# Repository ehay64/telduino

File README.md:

# Telduino

## Summary
Telduino is an Arduino shield for land line telephones. Telduino has the ability to send and receive audio to and from land line telephones, as well as make them ring.

## Background
Over the last few years, I've been collecting interesting land line telephones here and there. Since land line service is nearly defunct as of this writing, I figured it would be neat to have a device that could pipe audio to and from a telephone and, more importantly, make them ring. This culminated in an Arduino shield that can be connected to a telephone.

## Details
The heart of this shield is the KS0835F SLIC (subscriber line interface circuit) module. This module provides all the required voltages, currents, and signals to the telephone. It also provides line level audio input and output. The module itself requires some signaling, which is provided by the Arduino.

The shield has two 3.5mm audio jacks for audio input and output, and a RJ11 jack for the telephone. The Arduino sketch controls ringing of the telephone by controlling the SLIC module.

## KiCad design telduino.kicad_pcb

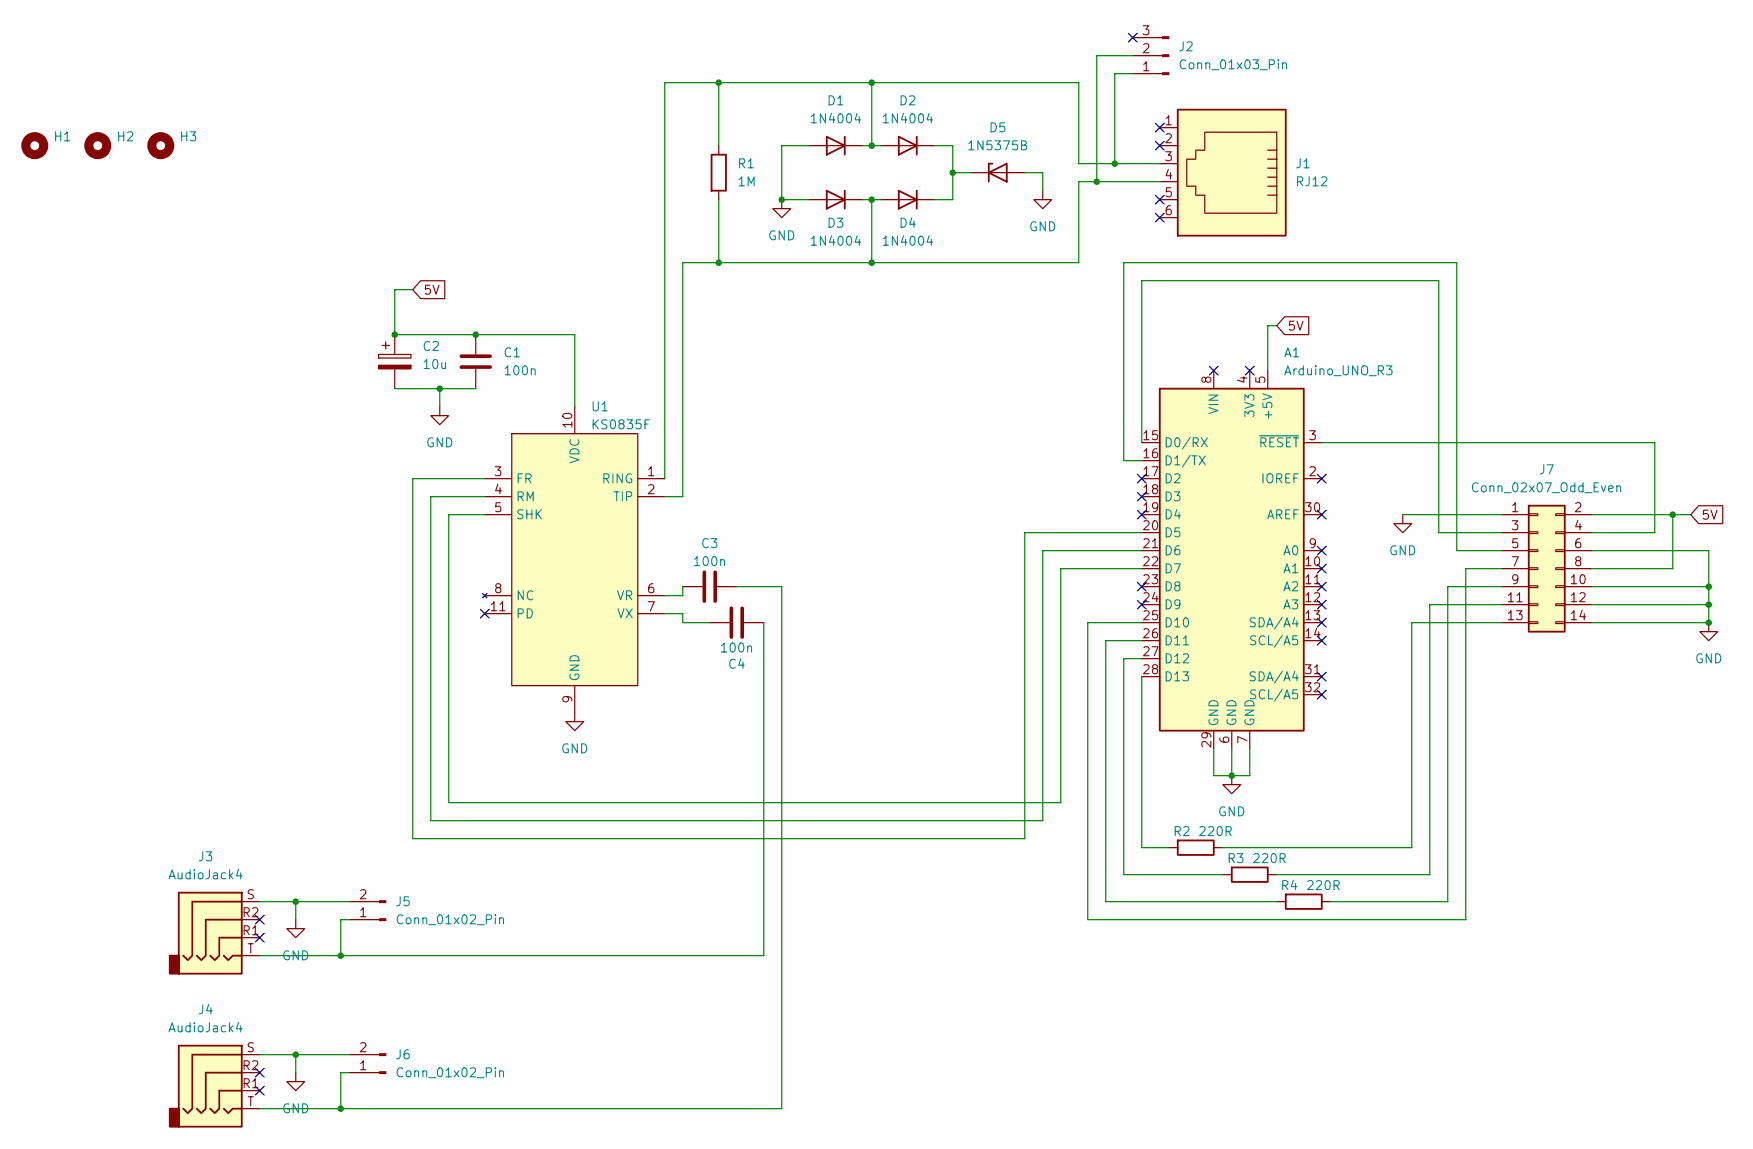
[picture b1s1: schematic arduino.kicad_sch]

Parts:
A1: Arduino_UNO_R3
C1, C3, C4: 100n; C_0805_2012Metric_Pad1.18x1.45mm_HandSolder
C2: 10u; CP_EIA-3216-18_Kemet-A_Pad1.58x1.35mm_HandSolder
D1, D2, D3, D4: 1N4004; D_DO-41_SOD81_P10.16mm_Horizontal
D5: 1N5375B; D_DO-201_P15.24mm_Horizontal
H1, H2, H3: MountingHole; MountingHole_3.2mm_M3
J1: RJ12; GCT_MJ3235-66-0_REVA
J2: Conn_01x03_Pin; PinHeader_1x03_P2.54mm_Vertical
J3, J4: AudioJack4; TENSILITY_54-00174
J5, J6: Conn_01x02_Pin; PinHeader_1x02_P2.54mm_Vertical
J7: Conn_02x07_Odd_Even; PinHeader_2x07_P2.54mm_Vertical
R1: 1M; R_Axial_DIN0207_L6.3mm_D2.5mm_P10.16mm_Horizontal
R2, R3, R4: 220R; R_0805_2012Metric_Pad1.20x1.40mm_HandSolder
U1: KS0835F

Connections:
5V: A1.5 (+5V), C1.1, C2.1, J7.2, J7.8, U1.10 (VDC)
GND: A1.6 (GND), A1.7 (GND), A1.29 (GND), C1.2, C2.2, D1.2 (A), D3.2 (A), D5.2 (A), J3.S, J4.S, J5.2, J6.2, J7.1, J7.6, J7.10, J7.12, J7.14, U1.9 (GND)
unnamed: A1.15 (D0/RX), J7.3
unnamed: A1.16 (D1/TX), J7.5
unnamed: A1.20 (D5), U1.3 (FR)
unnamed: A1.21 (D6), U1.4 (RM)
unnamed: A1.22 (D7), U1.5 (SHK)
unnamed: A1.25 (D10), J7.7
unnamed: A1.26 (D11), R4.2
unnamed: A1.27 (D12), R3.2
unnamed: A1.28 (D13), R2.2
unnamed: A1.3 (~RESET), J7.4
unnamed: D1.1 (K), D2.2 (A), J1.3, J2.1, R1.1, U1.1 (RING)
unnamed: D2.1 (K), D4.1 (K), D5.1 (K)
unnamed: D3.1 (K), D4.2 (A), J1.4, J2.2, R1.2, U1.2 (TIP)
unnamed: C4.2, J3.T, J5.1
unnamed: C3.2, J4.T, J6.1
unnamed: J7.9, R4.1
unnamed: J7.11, R3.1
unnamed: J7.13, R2.1
unnamed: C3.1, U1.6 (VR)
unnamed: C4.1, U1.7 (VX)

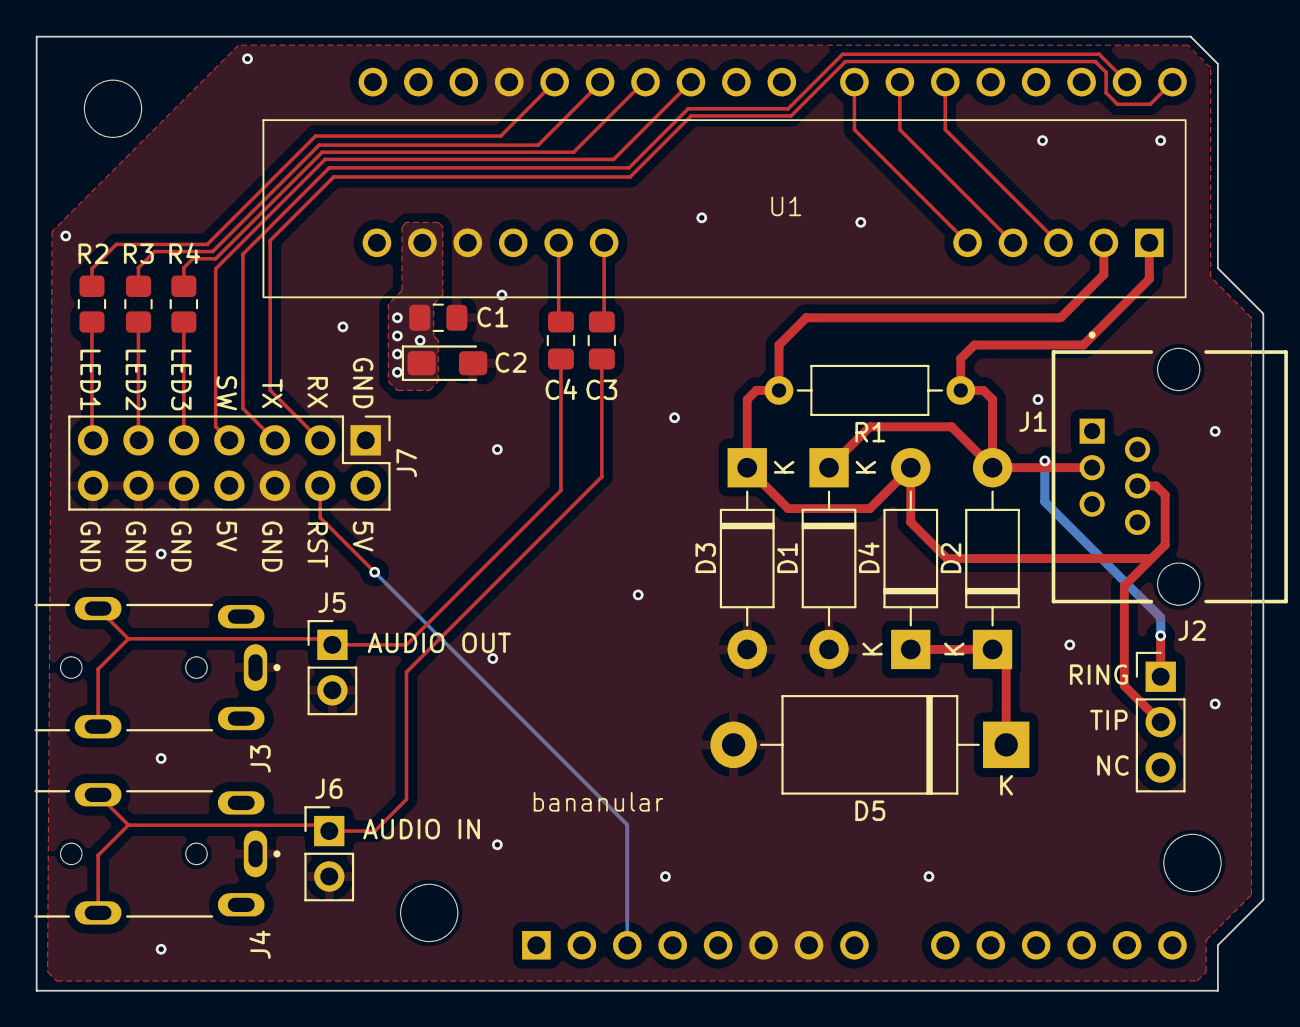
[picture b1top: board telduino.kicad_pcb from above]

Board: 2 copper layers, 68.6 x 53.3 mm, 25 parts (0 on the bottom side), 22 nets.

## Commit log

2025-07-07 Initial commit of KiCad project
2025-07-07 Update README.md
    Add general information to the README.
